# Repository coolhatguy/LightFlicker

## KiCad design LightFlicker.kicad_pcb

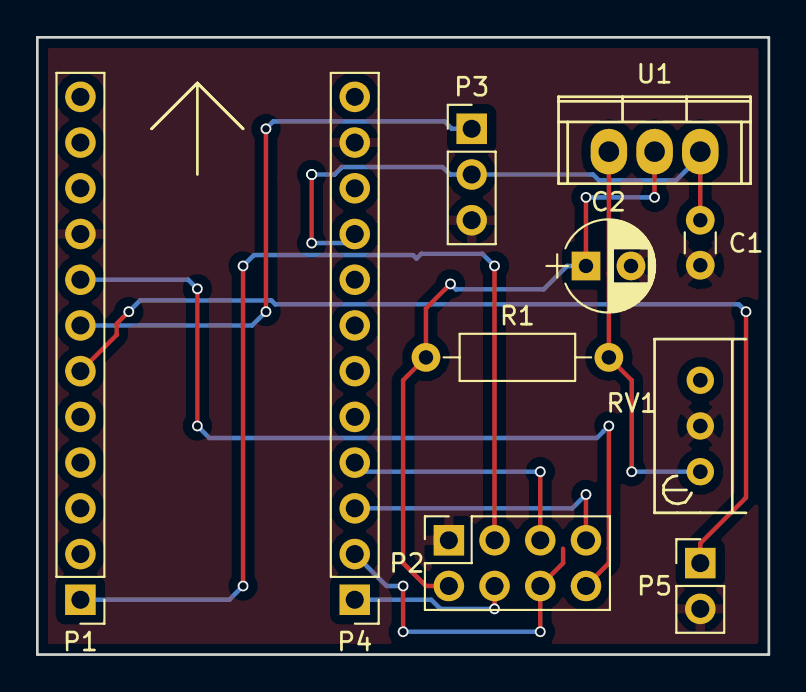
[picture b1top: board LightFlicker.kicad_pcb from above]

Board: 2 copper layers, 40.6 x 34.3 mm, 10 parts (0 on the bottom side), 12 nets.

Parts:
C1: 0.1 uF; C_Disc_D3.0mm_W1.6mm_P2.50mm
C2: 1 uF; CP_Radial_D5.0mm_P2.50mm
P1, P4: CONN_01X12; Socket_Strip_Straight_1x12_Pitch2.54mm
P2: CONN_02X04; Socket_Strip_Straight_2x04_Pitch2.54mm
P3: MG995 SERVO; Socket_Strip_Straight_1x03_Pitch2.54mm
P5: Button; Socket_Strip_Straight_1x02_Pitch2.54mm
R1: R; R_Axial_DIN0207_L6.3mm_D2.5mm_P10.16mm_Horizontal
RV1: POT_TRIM; Potentiometer_Bourns_3296W_3-8Zoll_Inline_ScrewUp
U1: LM317AT; TO-220

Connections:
+3V3: C2.1, P2.2, R1.1, U1.2
+5V: C1.1, P3.2, P4.9, U1.3
/CE: P1.1, P2.3
/CSN: P2.4, P4.1
/IRQ: P1.8, P2.8
/MISO: P2.7, P4.3
/MOSI: P2.6, P4.2
/PWM: P1.7, P3.1
/SCK: P2.5, P4.4
GND: C1.2, C2.2, P1.9, P2.1, P3.3, P4.11, P5.2, RV1.2
unnamed: P1.6, P5.1
unnamed: R1.2, RV1.1, U1.1
